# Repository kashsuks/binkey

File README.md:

# binkey
Binkey, short for binary keyboard is a small macropad that allows you to count using binary!! It uses 4 switches, 4 LED's, and a EC11 rotary encoder

## Why did I build this?

I made this as a part of Pathfinder, a You Ship We Ship for hackclub where you build a game controller with a few constraints.

## Images and Assets

Schematic:

PCB (Front):

PCB (Back):

## Code

The code was fully written in Arduino INO as one of the requirements for pathfinder was that the code must be written in C++. This left me to either use some really obscure and hard framework that took forever to learn, or learn Arduino INO.

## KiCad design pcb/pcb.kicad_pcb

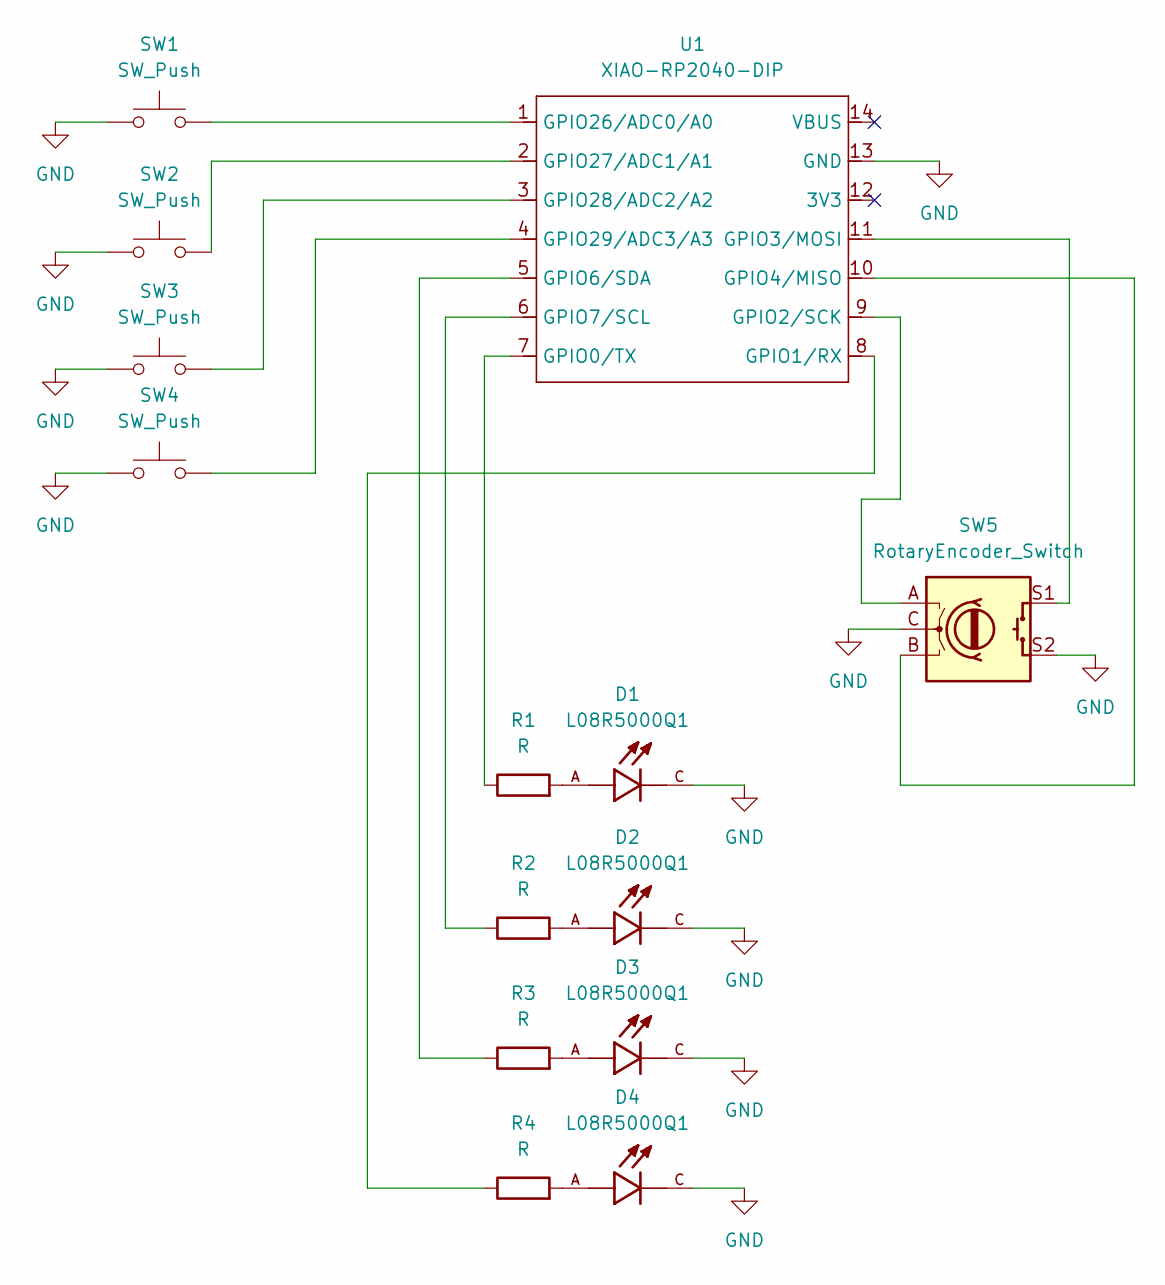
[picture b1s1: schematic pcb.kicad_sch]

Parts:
D1, D2, D3, D4: L08R5000Q1; LEDRD254W57D500H1070; PARTREV NA
R1, R2, R3, R4: R; R_Axial_DIN0204_L3.6mm_D1.6mm_P7.62mm_Horizontal
SW1, SW2, SW3, SW4: SW_Push; SW_Cherry_MX_1.00u_PCB
SW5: RotaryEncoder_Switch; RotaryEncoder_EC11
U1: XIAO-RP2040-DIP

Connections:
GND: D1.C, D2.C, D3.C, D4.C, SW1.1, SW2.1, SW3.1, SW4.1, SW5.C, SW5.S2, U1.13 (GND)
unnamed: D1.A, R1.2
unnamed: D2.A, R2.2
unnamed: D3.A, R3.2
unnamed: D4.A, R4.2
unnamed: R1.1, U1.7 (GPIO0/TX)
unnamed: R4.1, U1.8 (GPIO1/RX)
unnamed: SW5.A, U1.9 (GPIO2/SCK)
unnamed: SW5.S1, U1.11 (GPIO3/MOSI)
unnamed: SW5.B, U1.10 (GPIO4/MISO)
unnamed: R3.1, U1.5 (GPIO6/SDA)
unnamed: R2.1, U1.6 (GPIO7/SCL)
unnamed: SW1.2, U1.1 (GPIO26/ADC0/A0)
unnamed: SW2.2, U1.2 (GPIO27/ADC1/A1)
unnamed: SW3.2, U1.3 (GPIO28/ADC2/A2)
unnamed: SW4.2, U1.4 (GPIO29/ADC3/A3)

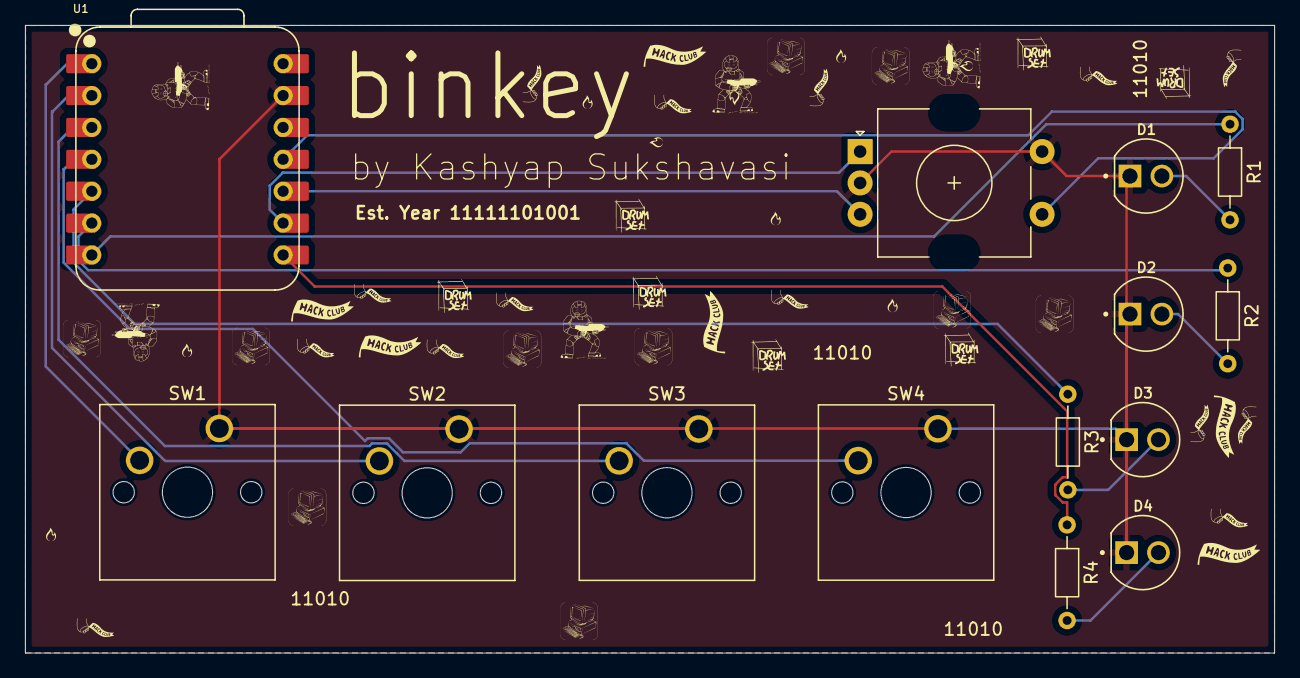
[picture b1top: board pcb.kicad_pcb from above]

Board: 2 copper layers, 99.5 x 50.0 mm, 14 parts (0 on the bottom side), 16 nets.

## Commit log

2025-06-29 added schematics!!!
2025-06-29 added the pcb too!!!
2025-06-29 gerbers
2025-06-30 updated pcb
2025-06-30 added gerbers stuff
2025-06-30 added extras
2025-07-04 added
2025-07-04 reverted
2025-07-04 push
2025-07-04 fixed
2025-07-04 holy shit these are my actual files
2025-07-04 added everything
2025-07-05 added my other file with the more complicated code as well
2025-07-05 added count down
2025-07-05 added the new countdown mode
2025-07-05 another count down thing yip yip
2025-07-05 added the readme
2025-07-05 added shit
